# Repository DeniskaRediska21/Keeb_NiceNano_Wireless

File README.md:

# Split Ergo Ortholinear Hotswap Keyboard based on supermini_nrf52840 (NiceNano clone) with Choc switches

This project attempts to create easelly reproducible split ortholinear hotswap mechanical
keyboard. 

Gimmics: 
+ This design doesn't require any diodes
+ Uses supermini_nrf52840 as MC, runs on CircuitPython
+ Key layouts are changed by dragging a file onto MC's storrage
+ Halves are connected through BLE
+ Conencts to PC through both BLE and wire
+ PCB fits into 100x100mm square, so it is very cheap to order from Chineese manifacturers
+ Uses Choc switches

# Gallery

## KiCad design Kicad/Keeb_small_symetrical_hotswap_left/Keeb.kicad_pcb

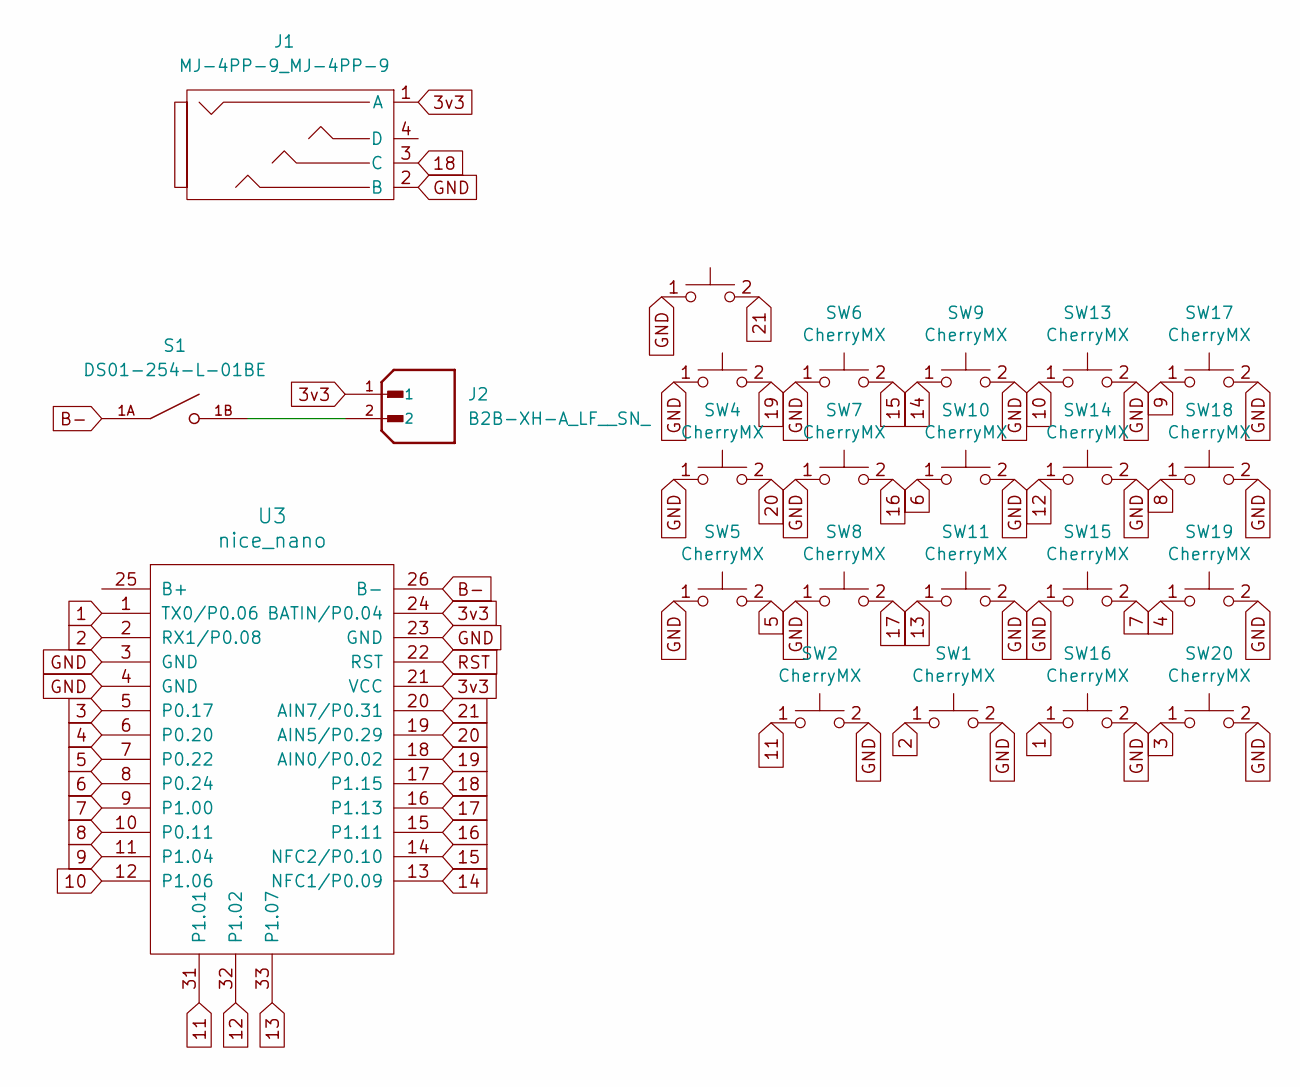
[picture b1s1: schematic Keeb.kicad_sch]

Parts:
J1: MJ-4PP-9_MJ-4PP-9; MJ-4PP-9
J2: B2B-XH-A_LF__SN_; JST_B2B-XH-A_LF__SN_; PARTREV N/A
S1: DS01-254-L-01BE; SW_DS01-254-L-01BE; PARTREV 1.0
SW1, SW2, SW3, SW4, SW5, SW6, SW7, SW8, SW9, SW10, SW11, SW12, SW13, SW14, SW15, SW16, SW17, SW18, SW19, SW20: CherryMX; Hotswap_Choc_V1_Plated_1.00u
U3: nice_nano

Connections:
1: SW16.1, U3.1 (TX0/P0.06)
2: SW1.1, U3.2 (RX1/P0.08)
3: SW20.1, U3.5 (P0.17)
3v3: J1.1 (A), J2.1, U3.21 (VCC), U3.24 (BATIN/P0.04)
4: SW19.1, U3.6 (P0.20)
5: SW5.2, U3.7 (P0.22)
6: SW10.1, U3.8 (P0.24)
7: SW15.2, U3.9 (P1.00)
8: SW18.1, U3.10 (P0.11)
9: SW17.1, U3.11 (P1.04)
10: SW13.1, U3.12 (P1.06)
11: SW2.1, U3.31 (P1.01)
12: SW14.1, U3.32 (P1.02)
13: SW11.1, U3.33 (P1.07)
14: SW9.1, U3.13 (NFC1/P0.09)
15: SW6.2, U3.14 (NFC2/P0.10)
16: SW7.2, U3.15 (P1.11)
17: SW8.2, U3.16 (P1.13)
18: J1.3 (C), U3.17 (P1.15)
19: SW3.2, U3.18 (AIN0/P0.02)
20: SW4.2, U3.19 (AIN5/P0.29)
21: SW12.2, U3.20 (AIN7/P0.31)
B-: S1.1A, U3.26 (B-)
GND: J1.2 (B), SW1.2, SW2.2, SW3.1, SW4.1, SW5.1, SW6.1, SW7.1, SW8.1, SW9.2, SW10.2, SW11.2, SW12.1, SW13.2, SW14.2, SW15.1, SW16.2, SW17.2, SW18.2, SW19.2, SW20.2, U3.3 (GND), U3.4 (GND), U3.23 (GND)
unnamed: J2.2, S1.1B
RST: U3.22 (RST)

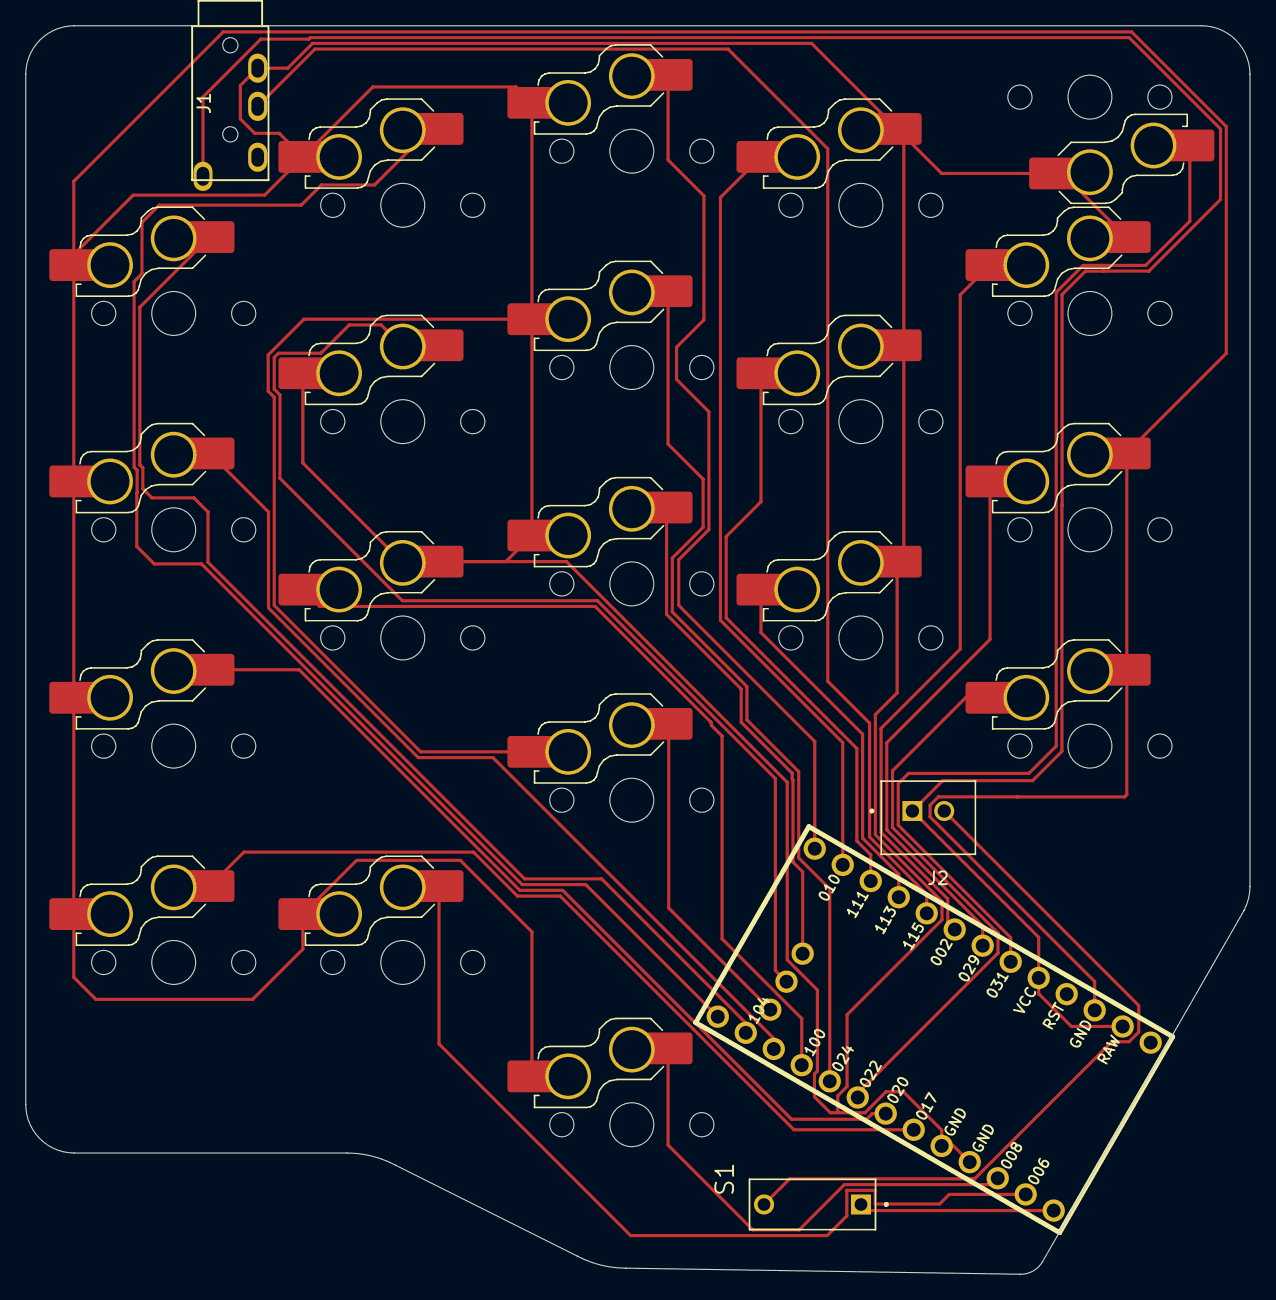
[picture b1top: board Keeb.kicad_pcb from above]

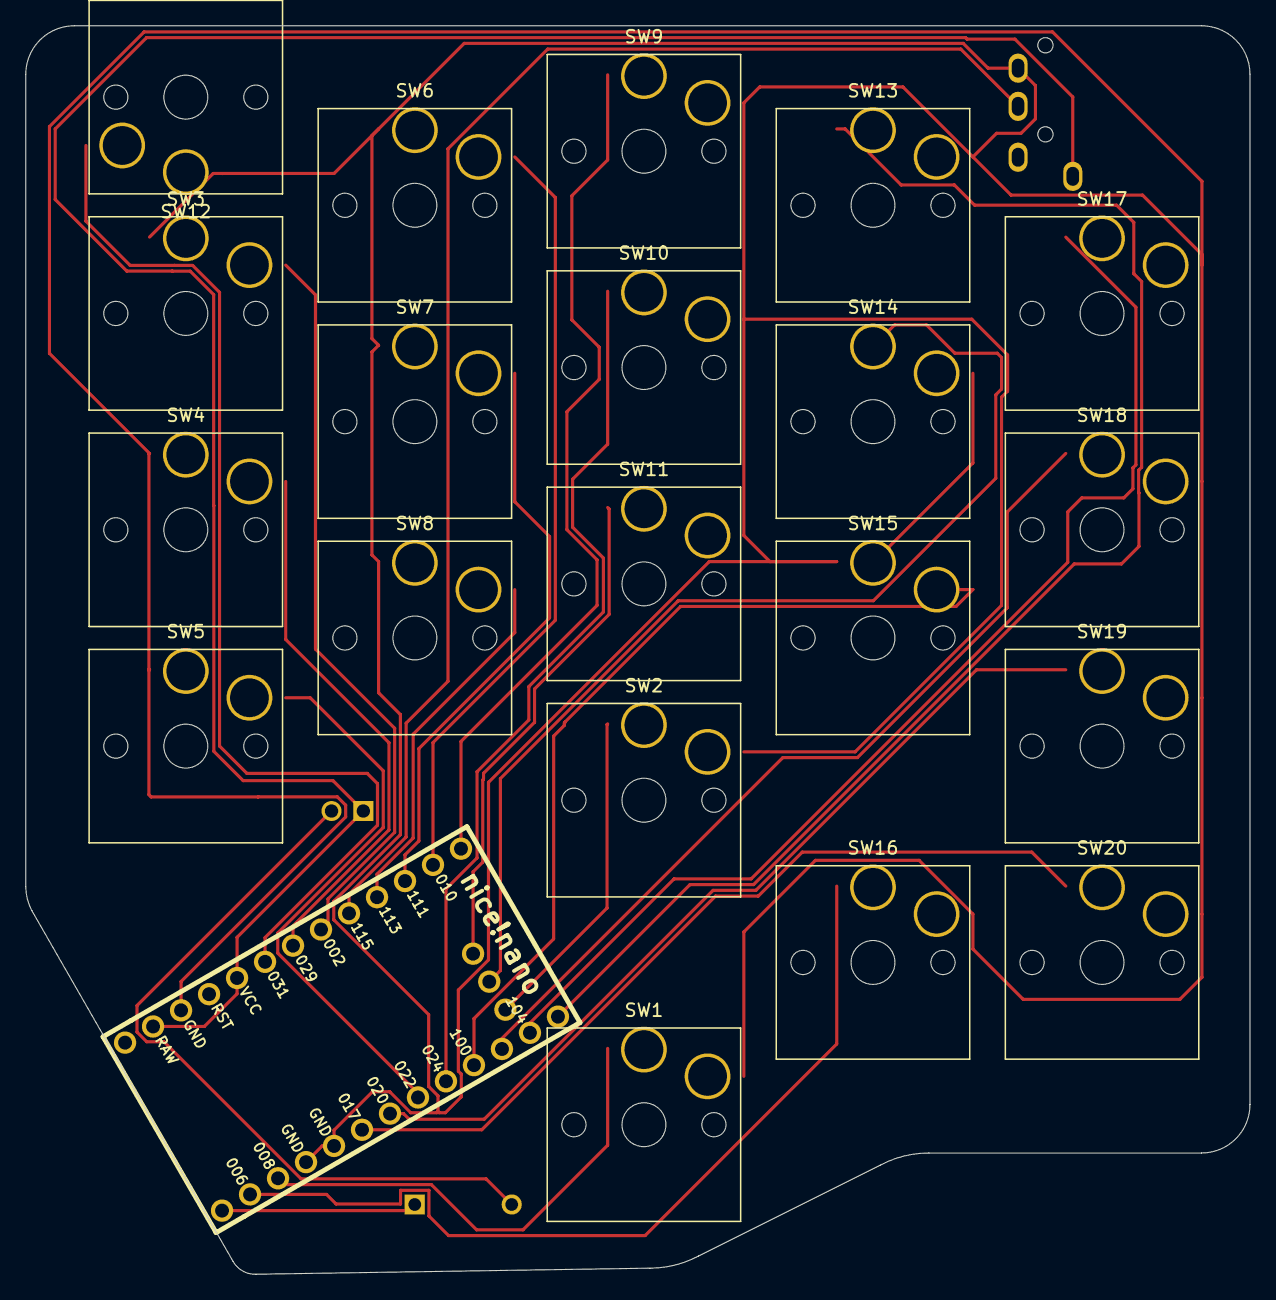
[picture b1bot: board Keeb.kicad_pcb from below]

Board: 2 copper layers, 96.2 x 98.1 mm, 24 parts (21 on the bottom side), 25 nets.

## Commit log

2025-04-09 current version, all problems fixed, software compiled for CP 9.0
2025-04-12 Work on gaskets started, now need to create laser files
